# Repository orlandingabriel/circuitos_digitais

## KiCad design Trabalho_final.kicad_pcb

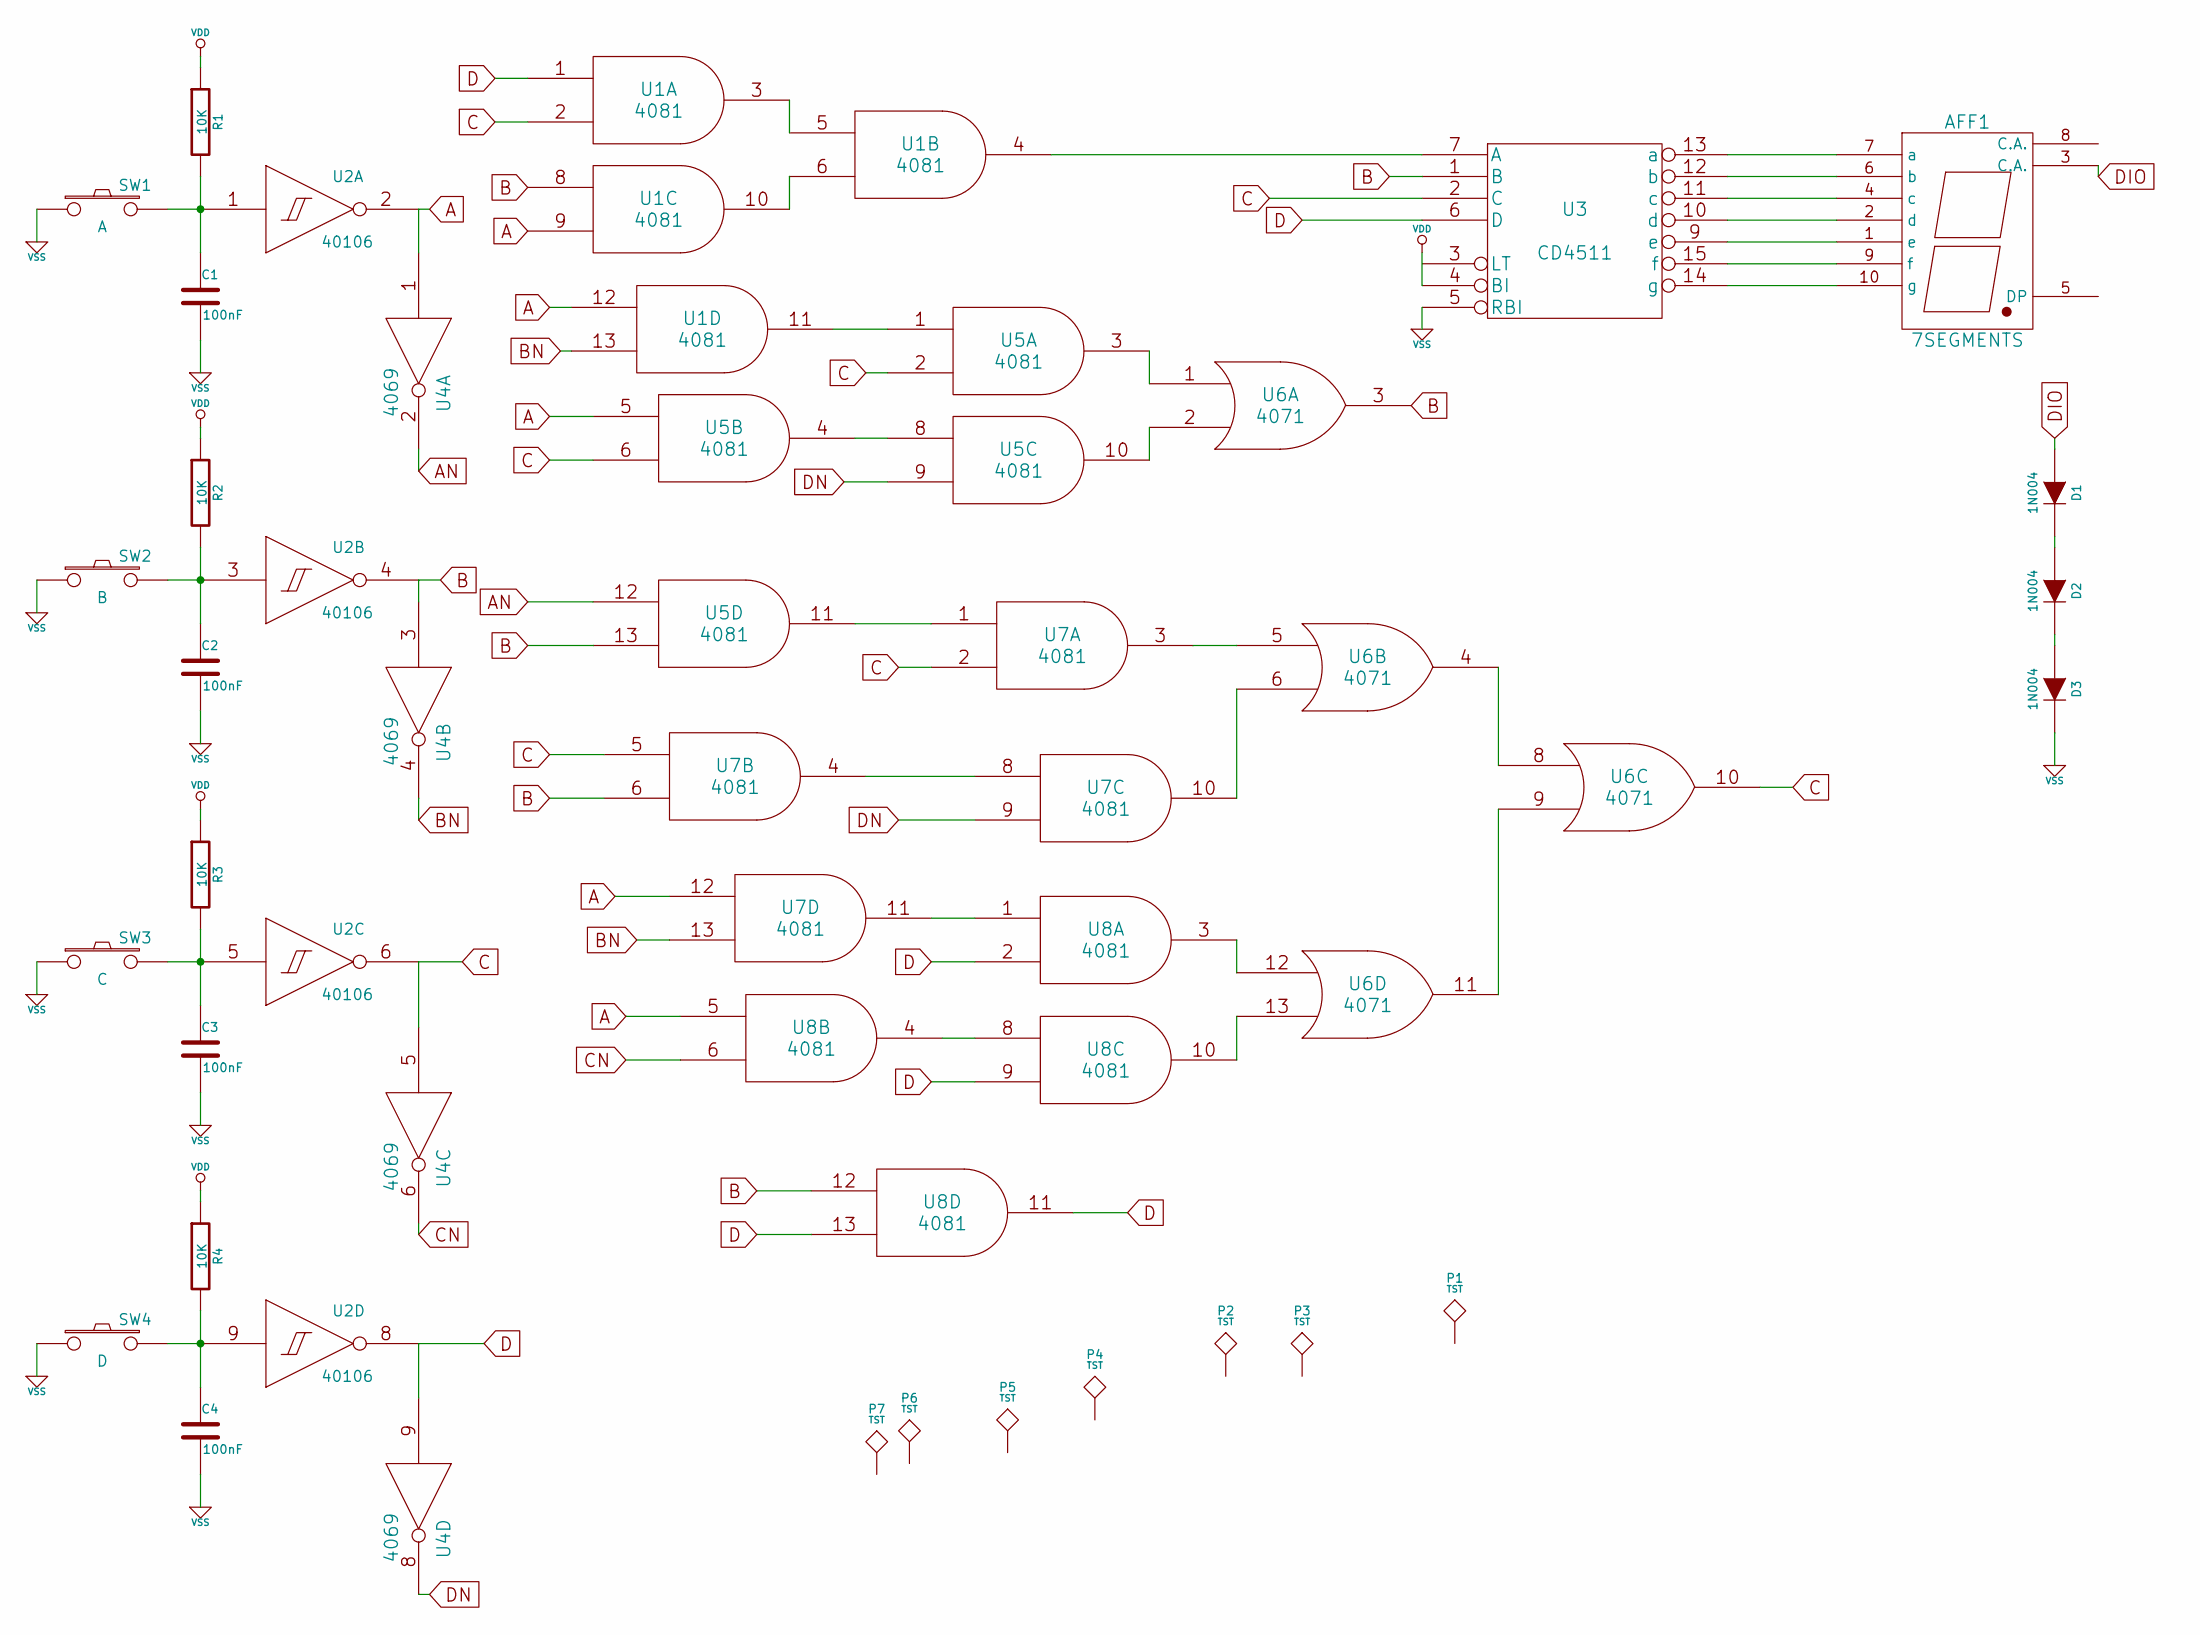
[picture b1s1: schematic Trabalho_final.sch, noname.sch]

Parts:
AFF1: 7SEGMENTS
C1, C2, C3, C4: 100nF
D1, D2, D3: 1N004
P1, P2, P3, P4, P5, P6, P7: TST
R1, R2, R3, R4: 10K
SW1: A
SW2: B
SW3: C
SW4: D
U1, U5, U7, U8: 4081
U2: 40106
U3: CD4511
U4: 4069
U6: 4071

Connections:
A: U1.9, U1.12, U2.2 (Out), U4.1, U5.5, U7.12, U8.5
AN: U4.2, U5.12
B: U1.8, U2.4 (Out), U3.1 (B), U4.3, U5.13, U6.3, U7.6, U8.12
BN: U1.13, U4.4, U7.13
C: U1.2, U2.6 (Out), U3.2 (C), U4.5, U5.2, U5.6, U6.10, U7.2, U7.5
CN: U4.6, U8.6
D: U1.1, U2.8 (Out), U3.6 (D), U4.9, U8.2, U8.9, U8.11, U8.13
DIO: AFF1.3 (C.A.), D1.1 (A)
DN: U4.8, U5.9, U7.9
unnamed: U1.3, U1.5
unnamed: U1.6, U1.10
unnamed: AFF1.10 (g), U3.14 (g)
unnamed: AFF1.9 (f), U3.15 (f)
unnamed: AFF1.1 (e), U3.9 (e)
unnamed: AFF1.2 (d), U3.10 (d)
unnamed: AFF1.4 (c), U3.11 (c)
unnamed: AFF1.6 (b), U3.12 (b)
unnamed: AFF1.7 (a), U3.13 (a)
unnamed: U5.3, U6.1
unnamed: C4.1, R4.2, SW4.2, U2.9 (In)
unnamed: C3.1, R3.2, SW3.2, U2.5 (In)
unnamed: U6.13, U8.10
unnamed: U1.4, U3.7 (A)
unnamed: U6.9, U6.11
unnamed: C1.1, R1.2, SW1.2, U2.1 (In)
unnamed: U6.12, U8.3
unnamed: U8.4, U8.8
unnamed: U7.11, U8.1
unnamed: U6.5, U7.3
unnamed: U6.6, U7.10
unnamed: U7.4, U7.8
unnamed: U5.11, U7.1
unnamed: U5.10, U6.2
unnamed: U5.4, U5.8
unnamed: U1.11, U5.1
unnamed: U6.4, U6.8
unnamed: C2.1, R2.2, SW2.2, U2.3 (In)
unnamed: D2.2 (K), D3.1 (A)
unnamed: D1.2 (K), D2.1 (A)
VDD: R1.1, R2.1, R3.1, R4.1, U1.14 (VDD), U2.14 (VDD), U3.4 (BI), U4.14 (VDD), U5.14 (VDD), U6.14 (VDD), U7.14 (VDD), U8.14 (VDD)
VSS: C1.2, C2.2, C3.2, C4.2, D3.2 (K), SW1.1, SW2.1, SW3.1, SW4.1, U1.7 (VSS), U2.7 (VSS), U3.5 (RBI), U4.7 (VSS), U5.7 (VSS), U6.7 (VSS), U7.7 (VSS), U8.7 (VSS)

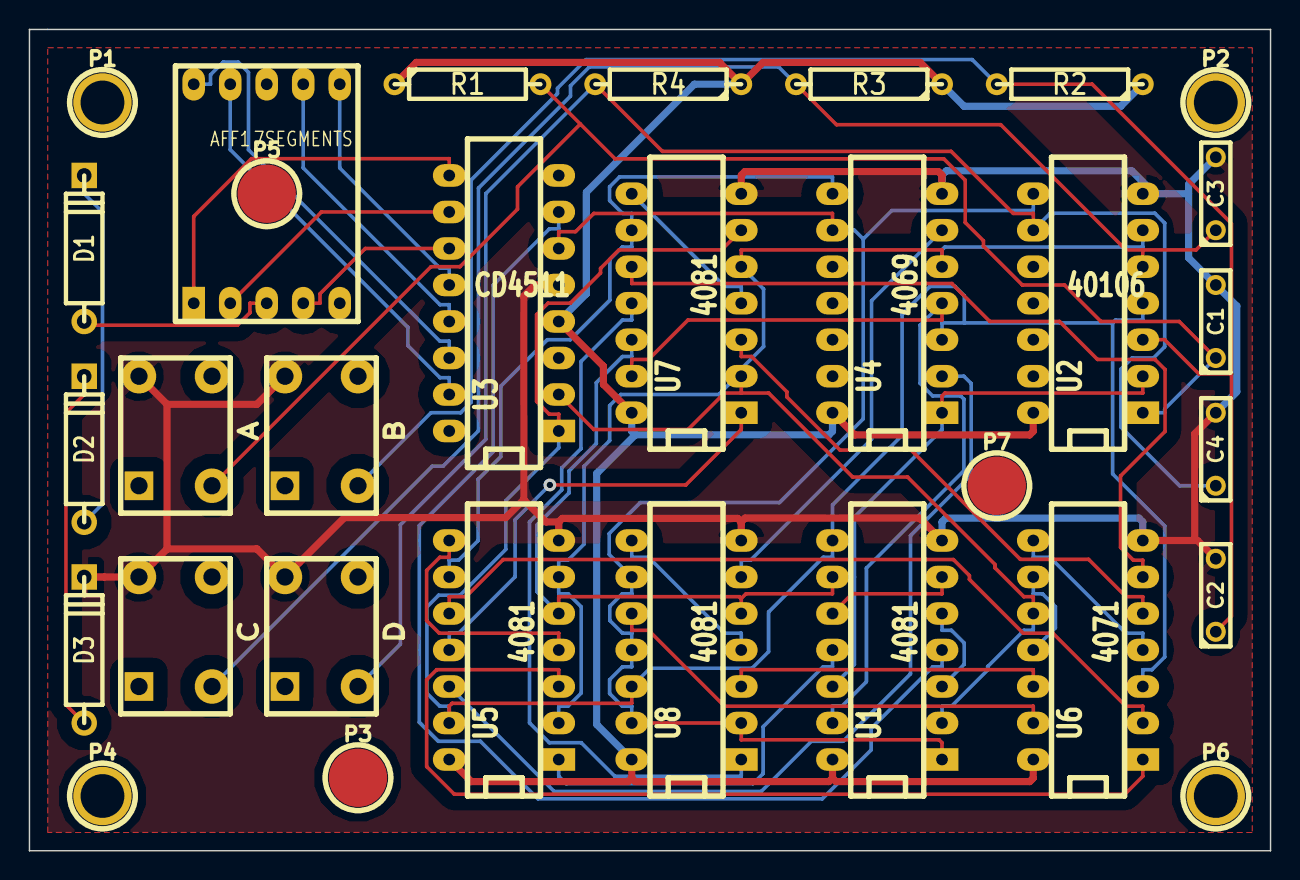
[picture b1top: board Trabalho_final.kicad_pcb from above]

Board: 2 copper layers, 86.4 x 57.2 mm, 31 parts (0 on the bottom side), 41 nets.

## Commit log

2022-09-14 commit inicial
